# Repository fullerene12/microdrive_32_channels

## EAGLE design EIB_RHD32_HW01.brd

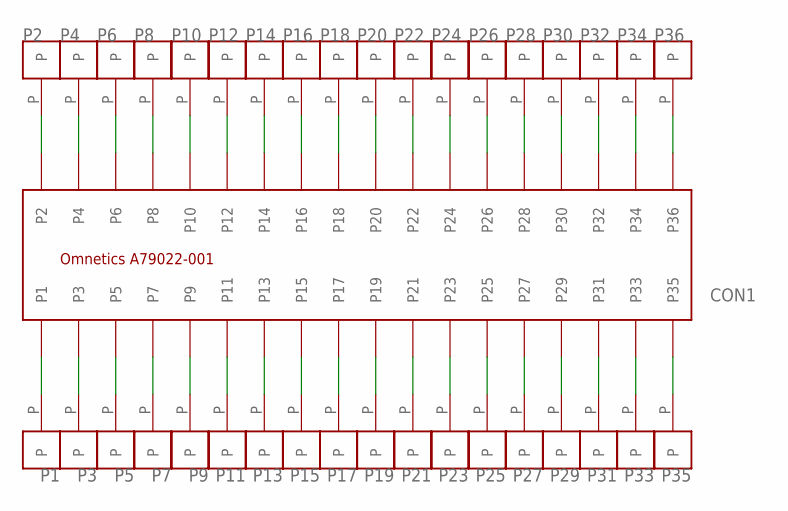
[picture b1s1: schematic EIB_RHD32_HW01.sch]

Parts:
CON1: A79022-001_MALESMD; A79026-001_MALE
P1, P2, P3, P4, P5, P6, P7, P8, P9, P10, P11, P12, P13, P14, P15, P16, P17, P18, P19, P20, P21, P22, P23, P24, P25, P26, P27, P28, P29, P30, P31, P32, P33, P34, P35, P36: EIB_SMALL_PIN

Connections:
unnamed: CON1.P1, P1.P
unnamed: CON1.P2, P2.P
unnamed: CON1.P3, P3.P
unnamed: CON1.P4, P4.P
unnamed: CON1.P5, P5.P
unnamed: CON1.P6, P6.P
unnamed: CON1.P7, P7.P
unnamed: CON1.P8, P8.P
unnamed: CON1.P9, P9.P
unnamed: CON1.P10, P10.P
unnamed: CON1.P11, P11.P
unnamed: CON1.P12, P12.P
unnamed: CON1.P13, P13.P
unnamed: CON1.P14, P14.P
unnamed: CON1.P15, P15.P
unnamed: CON1.P16, P16.P
unnamed: CON1.P17, P17.P
unnamed: CON1.P18, P18.P
unnamed: CON1.P19, P19.P
unnamed: CON1.P20, P20.P
unnamed: CON1.P21, P21.P
unnamed: CON1.P22, P22.P
unnamed: CON1.P23, P23.P
unnamed: CON1.P24, P24.P
unnamed: CON1.P25, P25.P
unnamed: CON1.P26, P26.P
unnamed: CON1.P27, P27.P
unnamed: CON1.P28, P28.P
unnamed: CON1.P29, P29.P
unnamed: CON1.P30, P30.P
unnamed: CON1.P31, P31.P
unnamed: CON1.P32, P32.P
unnamed: CON1.P33, P33.P
unnamed: CON1.P34, P34.P
unnamed: CON1.P35, P35.P
unnamed: CON1.P36, P36.P

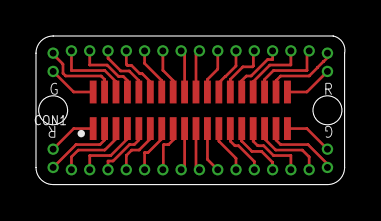
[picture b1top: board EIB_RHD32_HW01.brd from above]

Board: 2 copper layers, 17.2 x 8.3 mm, 37 parts (0 on the bottom side), 36 nets.

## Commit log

2018-05-12 -uploaded design files
